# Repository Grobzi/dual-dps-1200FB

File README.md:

# Dual DPS 1200FB 24V PSU

## Overview
This project demonstrates how to use two HP DPS-1200FB server PSUs in series to create a 24V power supply. An Arduino Nano R4 and a custom PCB are used to monitor and control the PSUs, with a 2.8" Arduino Shield-based touchscreen TFT for user interaction and data display.

## Features
- Monitoring of PSU parameters: current, power draw, temperature and many more.
- Touchscreen user interface (2.8" Arduino-compatible display)
- Control of 12V output in case of failure
- Basic statistics (consumed power per hour)

## Folder Structure
- `circuit/` - KiCad project files for the custom PCB (WIP)
- `doc/` - Documentation, datasheets, and images
- `src/` - Arduino firmware source code

## Firmware
1. Open `src/PsuPowerMonitor/PsuPowerMonitor.ino` in the Arduino IDE.
2. Install required libraries
    - [MCUFRIEND_kbv](https://github.com/prenticedavid/MCUFRIEND_kbv)
    - [Adafruit GFX Library](https://github.com/adafruit/Adafruit-GFX-Library)
3. Select the correct board and port.
4. Upload the firmware to your microcontroller.

## Contributing
Contributions are welcome! Please open issues or submit pull requests for improvements, bug fixes, or new features.

# Special thanks to
- [DrTune/Raplin](https://github.com/raplin/DPS-1200FB)
- [slundell](https://github.com/slundell/dps_charger)
- [colindt](https://colintd.blogspot.com/2016/10/hacking-hp-common-slot-power-supplies.html)
- [neilp](https://www.rcgroups.com/forums/showpost.php?p=48212083&postcount=29)
- [Philipp Seidel](https://blog.seidel-philipp.de/hp-dps-1200fb-power-supply-hack-for-charging-lipos/)

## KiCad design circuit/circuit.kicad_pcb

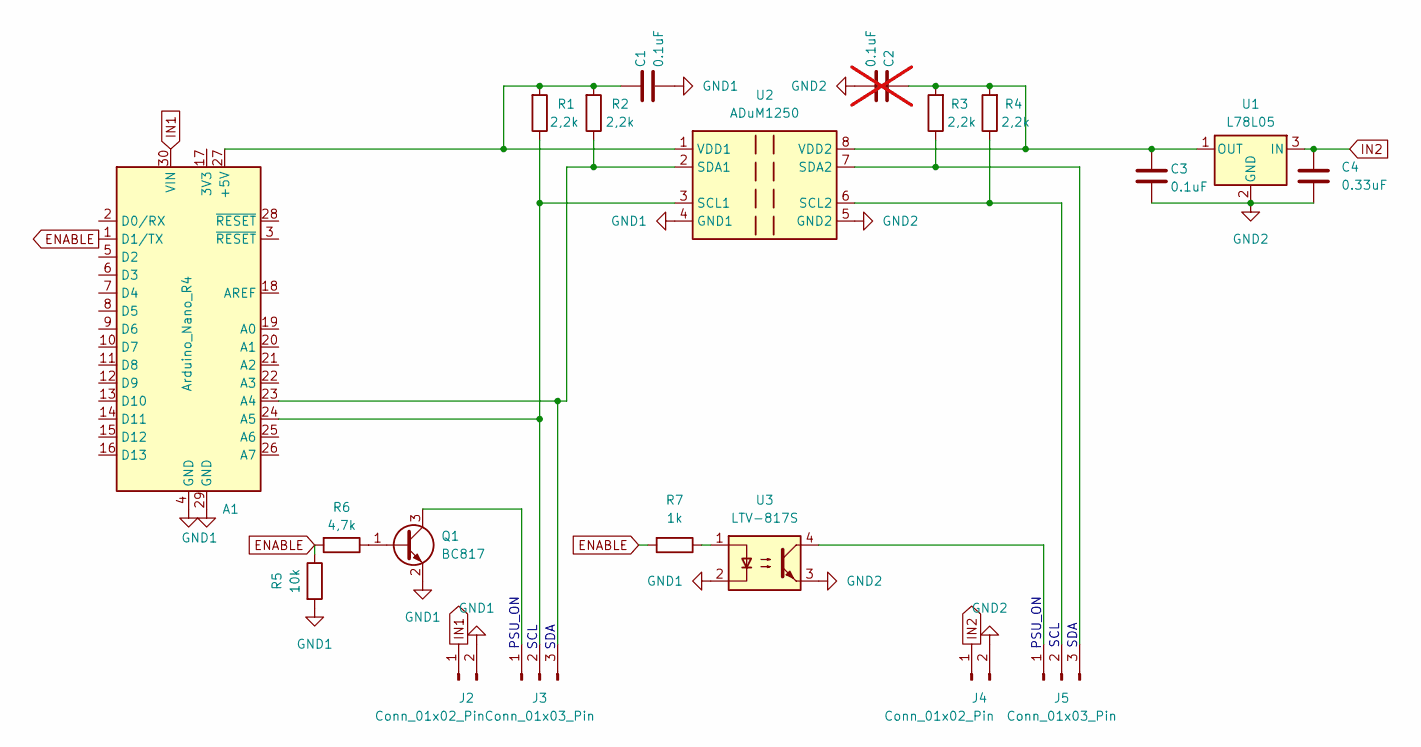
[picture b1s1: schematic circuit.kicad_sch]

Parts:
A1: Arduino_Nano_R4; Arduino_Nano
C1, C3: 0.1uF; C_0603_1608Metric; LCSC C125205
C2: 0.1uF; C_0603_1608Metric; not fitted
C4: 0.33uF; C_0603_1608Metric; LCSC C107070
J2, J4: Conn_01x02_Pin; PinHeader_1x02_P2.54mm_Vertical; LCSC C492401
J3, J5: Conn_01x03_Pin; PinHeader_1x03_P2.54mm_Vertical; LCSC C2937625
Q1: BC817; SOT-23
R1, R2, R3, R4: 2,2k; R_0603_1608Metric; LCSC C114662
R5: 10k; R_0603_1608Metric; LCSC C98220
R6: 4,7k; R_0603_1608Metric; LCSC C99782
R7: 1k; R_0603_1608Metric; LCSC C22548
U1: L78L05; SOT-89-3; LCSC C42738
U2: ADuM1250; SOIC-8_3.9x4.9mm_P1.27mm; LCSC C579378
U3: LTV-817S; SMDIP-4_W9.53mm; LCSC C109226

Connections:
ENABLE: A1.1 (D1/TX), R5.1, R6.2, R7.2
GND1: A1.4 (GND), A1.29 (GND), C1.2, J2.2, Q1.2 (E), R5.2, U2.4 (GND1), U3.2
GND2: C2.2, C3.2, C4.2, J4.2, U1.2 (GND), U2.5 (GND2), U3.3
IN1: A1.30 (VIN), J2.1
IN2: C4.1, J4.1, U1.3 (IN)
unnamed: A1.27 (+5V), C1.1, R1.2, R2.2, U2.1 (VDD1)
unnamed: A1.23 (A4), J3.3, R2.1, U2.2 (SDA1)
unnamed: A1.24 (A5), J3.2, R1.1, U2.3 (SCL1)
unnamed: J3.1, Q1.3 (C)
unnamed: J5.1, U3.4
unnamed: J5.2, R4.1, U2.6 (SCL2)
unnamed: J5.3, R3.1, U2.7 (SDA2)
unnamed: Q1.1 (B), R6.1
unnamed: R7.1, U3.1
unnamed: C2.1, C3.1, R3.2, R4.2, U1.1 (OUT), U2.8 (VDD2)

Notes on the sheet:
SCL
PSU_ON
SDA

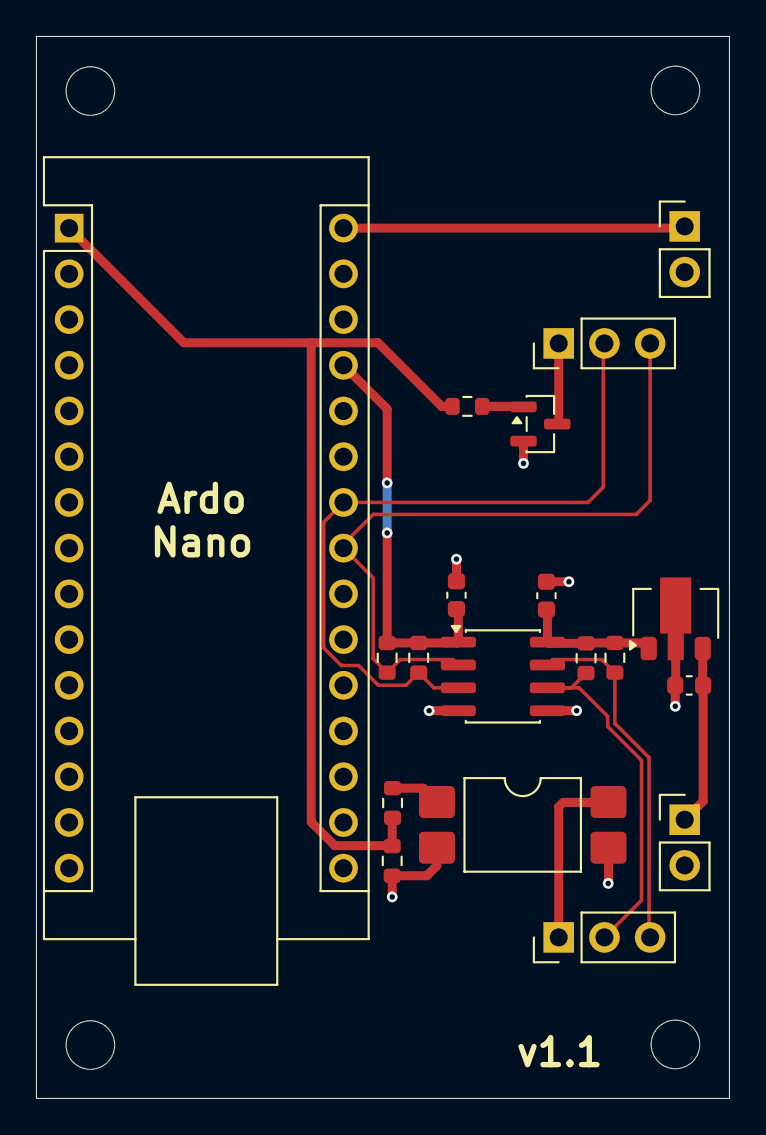
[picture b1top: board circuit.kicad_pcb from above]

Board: 2 copper layers, 38.5 x 59.0 mm, 19 parts (0 on the bottom side), 15 nets.

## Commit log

2025-09-25 added initial files
2025-10-15 Added formatting. Added enable pin logic.
2025-10-20 Added basic statistic collection and display.
2025-11-03 Updated PCB layout and circuit.
